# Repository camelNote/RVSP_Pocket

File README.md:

# RSVP Pocket 📖
</img>

## Overview
### <i> How fast can you read? </i><br>
Rapid Serial Visual Presentation is a reading technique of presenting text in a single focal point to reduce eye movement. The aim is maximize reading throughput without compromising understanding.<br>

RVSP Pocket is a STM32F4 "soft" fork of the [RSVP Nano](https://github.com/ionutdecebal/rsvpnano). RVSP Pocket aims to be a more hardware optimized version of the RVSP Nano, cheaper, and more compact. Currently the project is in the protyping stage, but here's the planned features pipeline:

> Features:
> * Localized simple Angular webapp to convert .epub files into .txt file that the MCU can decode quickly
> * Single cell battery charging circuitry with overvoltage & overcurrent protection. Power mux also included to reliably switch from battery power to USB when connected, removing the possibility of calibration error in charging circuit.
> * Can act as a USB Mass Storage Class (MSC) device: Allowing user to access microSD on their laptop! Essentially can act as an USB microSD card reader (which can cost anywhere from $15 to $30!)
> * 25 MHz external HSE that enables the STM32F4 family of chips to run at maximum rated system clock of 84 Mhz.

### Current board: (It looks better in person!)
</img>

## Bill of materials
BOM can be found at /PCB/RSVP_Pocket.csv
* Notes: (1) the only external part not included is the TFT screen. Please use 2.25" (76x284) display module with ST7789 Driver. (2) All of these parts are interchangeable with similarly speced components. Please ensure the footprints match though!

## Installation
This project is built using platformio which is a VS Code extension. You may also choose to flash the .elf (/.pio/build/genericsSTM32F401CC/firmware.elf) using the STM32CubeProgrammer.

Using Platformio:
1. Clone the repository.
2. Open the folder in VS Code and check the platformio.ini file. Ensure that it makes the specs of your components.
3. Program via either the Serial Wire Debug header pins or USB. In your platformio.ini file, make sure to define which upload protocol is being used:
> For SWD using an STlink: upload_protocol = stlink <br>
> For USB: upload_protocol = dfu

## PCB
### 3D view
</img>
</img>

### V1 Manufractured and soldered (by hand!)
</img>
</img>

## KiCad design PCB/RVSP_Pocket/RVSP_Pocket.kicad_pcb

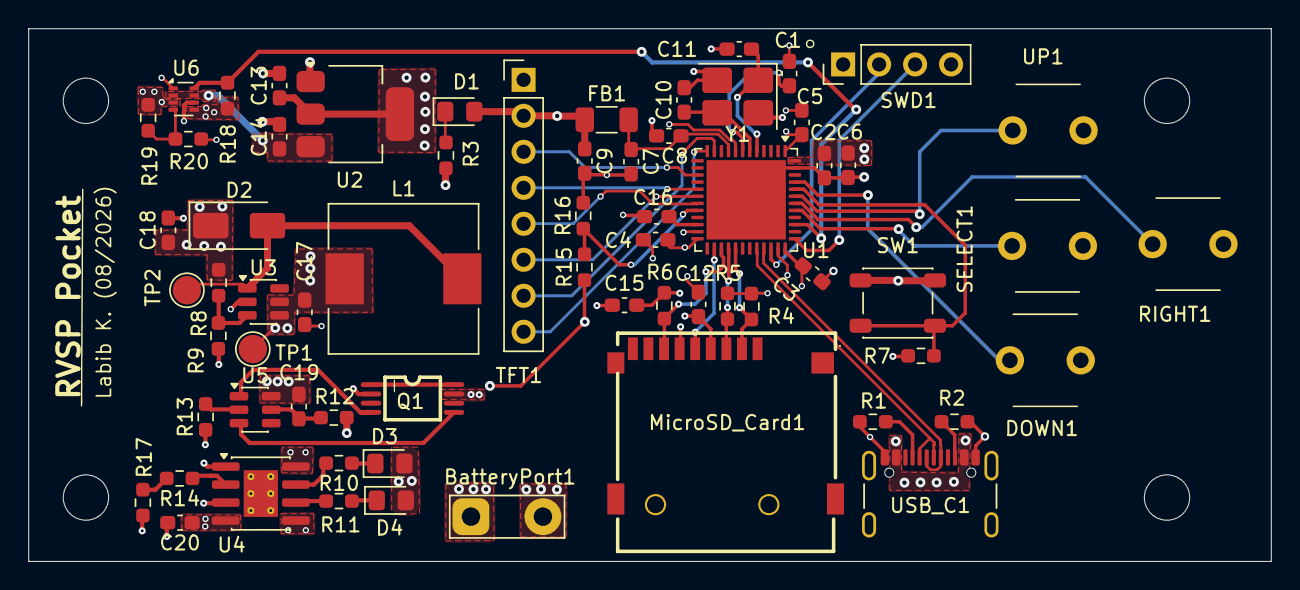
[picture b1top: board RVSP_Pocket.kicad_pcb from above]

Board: 4 copper layers, 87.7 x 37.6 mm, 70 parts (0 on the bottom side), 50 nets.

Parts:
BatteryPort1: Conn_01x02; TestPoint_2Pads_Pitch5.08mm_Drill1.3mm
C1, C2, C3, C4, C5, C12, C19: 100n; C_0603_1608Metric_Pad1.08x0.95mm_HandSolder
C6, C15, C20: 10u; C_0603_1608Metric_Pad1.08x0.95mm_HandSolder
C7, C9: 1u; C_0603_1608Metric_Pad1.08x0.95mm_HandSolder
C8: 10n; C_0603_1608Metric_Pad1.08x0.95mm_HandSolder
C10, C11: 10p; C_0603_1608Metric_Pad1.08x0.95mm_HandSolder
C13, C14: 22u; C_0603_1608Metric_Pad1.08x0.95mm_HandSolder
C16: 2.2u; C_0603_1608Metric_Pad1.08x0.95mm_HandSolder
C17, C18: 22uF; C_0603_1608Metric_Pad1.08x0.95mm_HandSolder
D1, D4: GREEN; LED_0805_2012Metric_Pad1.15x1.40mm_HandSolder
D2: SS34; D_SMA
D3: BLUE; LED_0805_2012Metric_Pad1.15x1.40mm_HandSolder
DOWN1: SW_Push; SW_PUSH_6mm_H5mm_2Leg
FB1: 220; R_1206_3216Metric_Pad1.30x1.75mm_HandSolder
H1, H2, H3, H4: MountingHole; MountingHole_3.2mm_M3_DIN965
L1: 22uH; L_10.4x10.4_H4.8
MicroSD_Card1: Micro_SD_Card; TF-SMD_XKTF-N02-N
Q1: 8205A_C5148694; TSSOP-8_L4.4-W3.0-P0.65-LS6.4-BL
R1, R2: 5.1k; R_0603_1608Metric_Pad0.98x0.95mm_HandSolder
R3, R10, R11, R14: 1k; R_0603_1608Metric_Pad0.98x0.95mm_HandSolder
R4, R5, R6, R18: 10k; R_0603_1608Metric_Pad0.98x0.95mm_HandSolder
R7: 43k; R_0603_1608Metric_Pad0.98x0.95mm_HandSolder
R8: 390k; R_0603_1608Metric_Pad0.98x0.95mm_HandSolder
R9: 51K; R_0603_1608Metric_Pad0.98x0.95mm_HandSolder
R12: 470; R_0603_1608Metric_Pad0.98x0.95mm_HandSolder
R13: 2k; R_0603_1608Metric_Pad0.98x0.95mm_HandSolder
R15, R16: 470k; R_0603_1608Metric_Pad0.98x0.95mm_HandSolder
R17: 150; R_0603_1608Metric_Pad0.98x0.95mm_HandSolder
R19, R20: 47k; R_0603_1608Metric_Pad0.98x0.95mm_HandSolder
RIGHT1: SW_Push; SW_PUSH_6mm_H5mm_2Leg
SELECT1: SW_Push; SW_PUSH_6mm_H5mm_2Leg
SW1: SW_Push; SW_SPST_PTS647_Sx38
SWD1: Conn_01x04_Pin; PinHeader_1x04_P2.54mm_Vertical
TFT1: Conn_01x08_Pin; PinHeader_1x08_P2.54mm_Vertical
TP1, TP2: TestPoint; TestPoint_Pad_D2.0mm
U1: STM32F401CCUx; QFN-48-1EP_7x7mm_P0.5mm_EP5.6x5.6mm
U2: AMS1117-3.3; SOT-223-3_TabPin2
U3: MT3608; SOT-23-6
U4: TP4056-42-ESOP8; SOIC-8-1EP_3.9x4.9mm_P1.27mm_EP2.41x3.3mm_ThermalVias
U5: DW01A; SOT-23-6
U6: TPS2116DRL; SOT-583-8
UP1: SW_Push; SW_PUSH_6mm_H5mm_2Leg
USB_C1: USB_C_Receptacle_USB2.0_16P; USB_C_Receptacle_GCT_USB4105-xx-A_16P_TopMnt_Horizontal
Y1: 25 Mhz; Crystal_SMD_3225-4Pin_3.2x2.5mm_HandSoldering

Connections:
+3V3: C2.1, C3.1, C4.1, C5.1, C6.1, C9.1, C12.1, C13.1, C15.1, D1.2 (A), FB1.1, MicroSD_Card1.4 (VDD), R4.1, R5.1, R6.1, SW1.1, SWD1.1, TFT1.2, U1.1 (VBAT), U1.24 (VDD), U1.36 (VDD), U1.48 (VDD), U2.2 (VO)
/BAT_LVL: R15.2, R16.1, U1.20 (PB2)
/BAT_Neg: BatteryPort1.2, C19.2, Q1.7 (S2), U5.6 (GND)
/BAT_ON: R18.1, U1.39 (PB3), U6.8 (ST)
/BOOT0: R7.1, SW1.2, U1.44 (BOOT0)
/D1: Q1.1 (D1), Q1.8 (D2)
/DWN_BTN: DOWN1.1, U1.45 (PB8)
/HSE_IN: C11.1, U1.5 (PH0), Y1.1
/HSE_OUT: C10.1, U1.6 (PH1), Y1.3
/NRST: C1.1, U1.7 (NRST)
/OC: Q1.5 (G2), U5.3 (OC)
/OD: Q1.4 (G1), U5.1 (OD)
/PR1: R19.2, R20.1, U6.4 (PR1)
/PROG: R14.1, U4.2 (PROG)
/RIGHT_BTN: RIGHT1.1, U1.42 (PB6)
/SD_CLK: MicroSD_Card1.5 (CLK), U1.26 (PB13)
/SD_CS: MicroSD_Card1.2 (DAT3/CD), R4.2, U1.29 (PA8)
/SD_MISO: MicroSD_Card1.7 (DAT0), R6.2, U1.27 (PB14)
/SD_MOSI: MicroSD_Card1.3 (CMD), R5.2, U1.28 (PB15)
/SELECT_BTN: SELECT1.1, U1.41 (PB5)
/SWCLK: SWD1.3, U1.37 (PA14)
/SWDIO: SWD1.2, U1.34 (PA13)
/TFT_BL: TFT1.8, U1.12 (PA2)
/TFT_CS: TFT1.7, U1.11 (PA1)
/TFT_DC: TFT1.6, U1.18 (PB0)
/TFT_MOSI: TFT1.4, U1.17 (PA7)
/TFT_RST: TFT1.5, U1.19 (PB1)
/TFT_SCLK: TFT1.3, U1.15 (PA5)
/UP_BTN: U1.43 (PB7), UP1.1
/USB_D+: U1.33 (PA12), USB_C1.A6 (D+), USB_C1.B6 (D+)
/USB_D-: U1.32 (PA11), USB_C1.A7 (D-), USB_C1.B7 (D-)
/VREF+: C7.1, C8.1, FB1.2, U1.9 (VREF+)
/~CHRG: R10.2, U4.7 (~CHRG)
/~STDBY: R11.2, U4.6 (~STDBY)
BAT_5V: C18.1, D2.1 (K), R8.1, U6.6 (VIN2)
BAT_Pos: BatteryPort1.1, C17.1, L1.1, R12.1, R15.1, TP1.1 (1_1), U3.4 (EN), U3.5 (IN), U4.5 (BAT)
GND: C1.2, C2.2, C3.2, C4.2, C5.2, C6.2, C7.2, C8.2, C9.2, C10.2, C11.2, C12.2, C13.2, C14.2, C15.2, C16.2, C17.2, C18.2, C20.2, DOWN1.2, MicroSD_Card1.6 (VSS), Q1.2 (S1), R1.1, R2.1, R3.2, R7.2, R9.2, R13.1, R16.2, R17.2, R20.2, RIGHT1.2, SELECT1.2, SWD1.4, TFT1.1, U1.8 (VSSA), U1.23 (VSS), U1.35 (VSS), U1.47 (VSS), U1.49 (VSS), U2.1 (GND), U3.2 (GND), U4.1 (TEMP), U4.3 (GND), U4.9 (EPAD), U6.1 (GND), UP1.2, USB_C1.A1 (GND), USB_C1.A12 (GND), USB_C1.B1 (GND), USB_C1.B12 (GND), Y1.2 (G), Y1.4 (G)
unnamed: D1.1 (K), R3.1
unnamed: D2.2 (A), L1.2, TP2.1 (1_1), U3.1 (SW)
unnamed: D3.1 (K), R10.1
unnamed: D4.1 (K), R11.1
unnamed: R14.2, R17.1
unnamed: C16.1, U1.22 (VCAP1)
unnamed: R8.2, R9.1, U3.3 (FB)
unnamed: R13.2, U5.2 (CS)
unnamed: C19.1, R12.2, U5.5 (VCC)
unnamed: R1.2, USB_C1.A5 (CC1)
unnamed: R2.2, USB_C1.B5 (CC2)
REG_IN: C14.1, U2.3 (VI), U6.2 (VOUT), U6.7 (VOUT)
VBUS: C20.1, D3.2 (A), D4.2 (A), R18.2, R19.1, U4.4 (V_{CC}), U4.8 (CE), U6.3 (VIN1), U6.5 (MODE), USB_C1.A4 (VBUS), USB_C1.A9 (VBUS), USB_C1.B4 (VBUS), USB_C1.B9 (VBUS)

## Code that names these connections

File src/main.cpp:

#include <Arduino.h>
#include <TFT_eSPI.h>

#include <NotoSansJP20.h>
#include "WordProcess.h"
#include "Menu.h"

/* Const variable definitions */
//Fonts
#define AA_FONT_SMALL NotoSansJP20
#define GFXFF 1

//Reversed due to landscape mode
#define HALF_WIDTH TFT_HEIGHT/2
#define HALF_HEIGHT TFT_WIDTH/2

#define SD_CS PA8

//Button definitions
#define RIGHT_BTN PB6
#define SELECT_BTN PB5
#define UP_BTN PB7
#define DOWN_BTN PB8

SPIClass mySPI(PB15, PB14, PB13); //MOSI, MISO, CLK, SSEL
SdSpiConfig sdSdioConfig(SD_CS, DEDICATED_SPI, SD_SCK_MHZ(40), &mySPI);

/* Global variables */
volatile bool rightBtnPressed = false;
volatile bool selectBtnPressed = false;
volatile bool upBtnPressed = false;
volatile bool downBtnPressed = false;

SdFat sd;
File32 bookFile;

TFT_eSPI tft = TFT_eSPI();

btnSelection btnStates = {0, 0, 0}; // Initialize all states to 0

char wordBuffer[WORDS_PER_CHUNK][MAX_WORD_LEN];
uint64_t endPos = 0;//Track position of cursor
int32_t readCount; //Number of words read from file

uint16_t wordSpeed = 300; //Default wpm speed;
uint16_t brightness = 100;
uint32_t delayTime = (float)60/wordSpeed * 1000; //ms delay between words

volatile unsigned long lastInterruptTime = 0;
const unsigned long debounceDelay = 20; // ms

// ISR
void rightBtnISR(){
  unsigned long currentTime = millis();
  if (currentTime - lastInterruptTime >= debounceDelay) {
    rightBtnPressed = true; 
    lastInterruptTime = currentTime;
    btnStates.menuState = (btnStates.menuState + 1) % 4; //Cycle through menu states
  }
}

void selectBtnISR(){
  unsigned long currentTime = millis();
  if (currentTime - lastInterruptTime >= debounceDelay*3) {
    selectBtnPressed = true; 
    lastInterruptTime = currentTime;
    btnStates.selectState = 1; // Toggle select state
  }
}

void upBtnISR(){
  unsigned long currentTime = millis();
  if (currentTime - lastInterruptTime >= debounceDelay) {
    upBtnPressed = true; 
    lastInterruptTime = currentTime;
    btnStates.upDownCounter += 1;
  }
}

void downBtnISR(){
  unsigned long currentTime = millis();
  if (currentTime - lastInterruptTime >= debounceDelay) {
    downBtnPressed = true; // toggle button state
    lastInterruptTime = currentTime;
    btnStates.upDownCounter = (btnStates.upDownCounter > 0)? btnStates.upDownCounter - 1: 0;
  }
}

void setup() {
  //PinMode declarations
  pinMode(RIGHT_BTN, INPUT_PULLUP);//Button
  pinMode(SELECT_BTN, INPUT_PULLUP);
  pinMode(UP_BTN, INPUT_PULLUP); 
  pinMode(DOWN_BTN, INPUT_PULLUP);
  pinMode(PC15, OUTPUT);
  pinMode(PA2, OUTPUT);

  digitalWrite(PC15, LOW);//Virtual GND
  digitalWrite(PA2, LOW);//TFT BL LOW 
  

  bool sdOK = sd.begin(sdSdioConfig);   // no "bool" — assigns the global
  //uint8_t errCode = sd.sdErrorCode();                   // no "uint8_t"
  //uint8_t errData = sd.sdErrorData();

  //Interrupts
  attachInterrupt(RIGHT_BTN, rightBtnISR, FALLING); //Active low button
  attachInterrupt(SELECT_BTN, selectBtnISR, FALLING);
  attachInterrupt(UP_BTN, upBtnISR, FALLING);
  attachInterrupt(DOWN_BTN, downBtnISR, FALLING);

  tft.init();
  tft.setRotation(3);
  tft.fillScreen(TFT_BLACK);

  if(!sdOK){
    //bookFile = sd.open("rvsp/book01.txt", FILE_READ);
    // Handle SD card initialization failure
    while(true){
      drawRVSPWord("SD_Failed", HALF_WIDTH, HALF_HEIGHT, &tft);
      delay(5000);
    } 
  }//if
}

void loop() {
  drawMenu(&tft, &btnStates, sd, bookFile, sdSdioConfig, wordSpeed, brightness);

  //Setting Constants
  delayTime = (float)60/wordSpeed * 1000;

  tft.loadFont(AA_FONT_SMALL);
  tft.setTextColor(TFT_WHITE, TFT_BLACK);
  tft.setTextDatum(MC_DATUM);
  
  drawRVSPWord("Start", HALF_WIDTH, HALF_HEIGHT, &tft);
  readCount = fetchWords(wordBuffer, &bookFile, endPos, &endPos);

  rightBtnPressed = false;
  selectBtnPressed =  false;

  tft.drawLine(143, 0, 143, 14, 0xFFFF);
  tft.drawLine(143, 61, 143, 75, 0xFFFF);
  
  while(readCount > 0){
    uint8_t counter = 0;

    while(counter < WORDS_PER_CHUNK){
      if(selectBtnPressed){
        rightBtnPressed = false;
        selectBtnPressed = false;

        //Pause
        while(!rightBtnPressed){
          if(selectBtnPressed) break;
          delay(200);
        }
        break;
      }//if
      else if(rightBtnPressed){
        drawRVSPWord(wordBuffer[counter], HALF_WIDTH, HALF_HEIGHT, &tft);
          uint8_t wordLength = strlen(wordBuffer[counter]);
          char lastChar = wordBuffer[counter][wordLength - 1];

          //Add extra delay for punctuation
          if(lastChar == '.' || lastChar == '?' || lastChar == '!' || lastChar == ',') {
            delay(delayTime * 2); 
          }else {
            delay(delayTime);
          }
          counter++;
      }//else if
    }//while

    if(selectBtnPressed && rightBtnPressed) break;

    //Fetch another batch
    readCount = fetchWords(wordBuffer, &bookFile, endPos, &endPos);

  }//while

  //End of book reached
  if(readCount == 0){
    bookFile.seek(0);
    endPos = 0;
    readCount = fetchWords(wordBuffer, &bookFile, 0, &endPos);
    drawRVSPWord("End of book", HALF_WIDTH, HALF_HEIGHT, &tft);
    delay(1000);
  }
  
  
  rightBtnPressed = false;
  selectBtnPressed =  false;
  drawRVSPWord("Returning to Menu", HALF_WIDTH, HALF_HEIGHT, &tft);
  delay(1000);
  btnStates = {0,0,0};
}
